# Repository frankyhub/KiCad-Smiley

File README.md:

<div align="center">

|[:skull:ISSUE](https://github.com/frankyhub/KiCad-Smiley/issues?q=is%3Aissue)|[:speech_balloon: Forum /Discussion](https://github.com/frankyhub/KiCad-Smiley/discussions)|[:grey_question:WiKi](https://github.com/frankyhub/KiCad-Smiley/wiki)||
|--|--|--|--|
| | | | |
<a href="https://github.com/frankyhub/KiCad-Smiley/issues">|<a href="https://github.com/frankyhub/KiCad-Smiley/discussions">|<a href="https://github.com/frankyhub/KiCad-Smiley/6eleases">||
|| <a href="https://github.com/frankyhub/KiCad-Smiley/pulse" alt="Activity">| <a href="https://github.com/frankyhub/KiCad-Smiley/graphs/traffic">  |<a href="https://github.com/frankyhub?tab=stars"> ||

</div>

## Smiley

<br> <br>

### BOM

| Anzahl | Bezeichnung | 
| -------- | -------- | 
|  1 |   NE555 |
| 1  |  CD4017|
| 15  |  LED rt  |
| 1  | 10uF   |
|  2 |  100R  |
| 1  | 1,2k   |
| 1  | 100k Trimmer   |
| 1  | Microschalter   |
| 2  | Batterieclipps   |
| 2  |  CR2032  |
| 1  |  Foldback-Klammern 15mm  |
| -------- | -------- | 

---

<div style="position:absolute; left:2cm; ">   
<ol class="breadcrumb" style="border-top: 2px solid black;border-bottom:2px solid black; height: 45px; width: 900px;"> <p align="center"><a href="#oben">nach oben</a></p></ol>
</div>  

---

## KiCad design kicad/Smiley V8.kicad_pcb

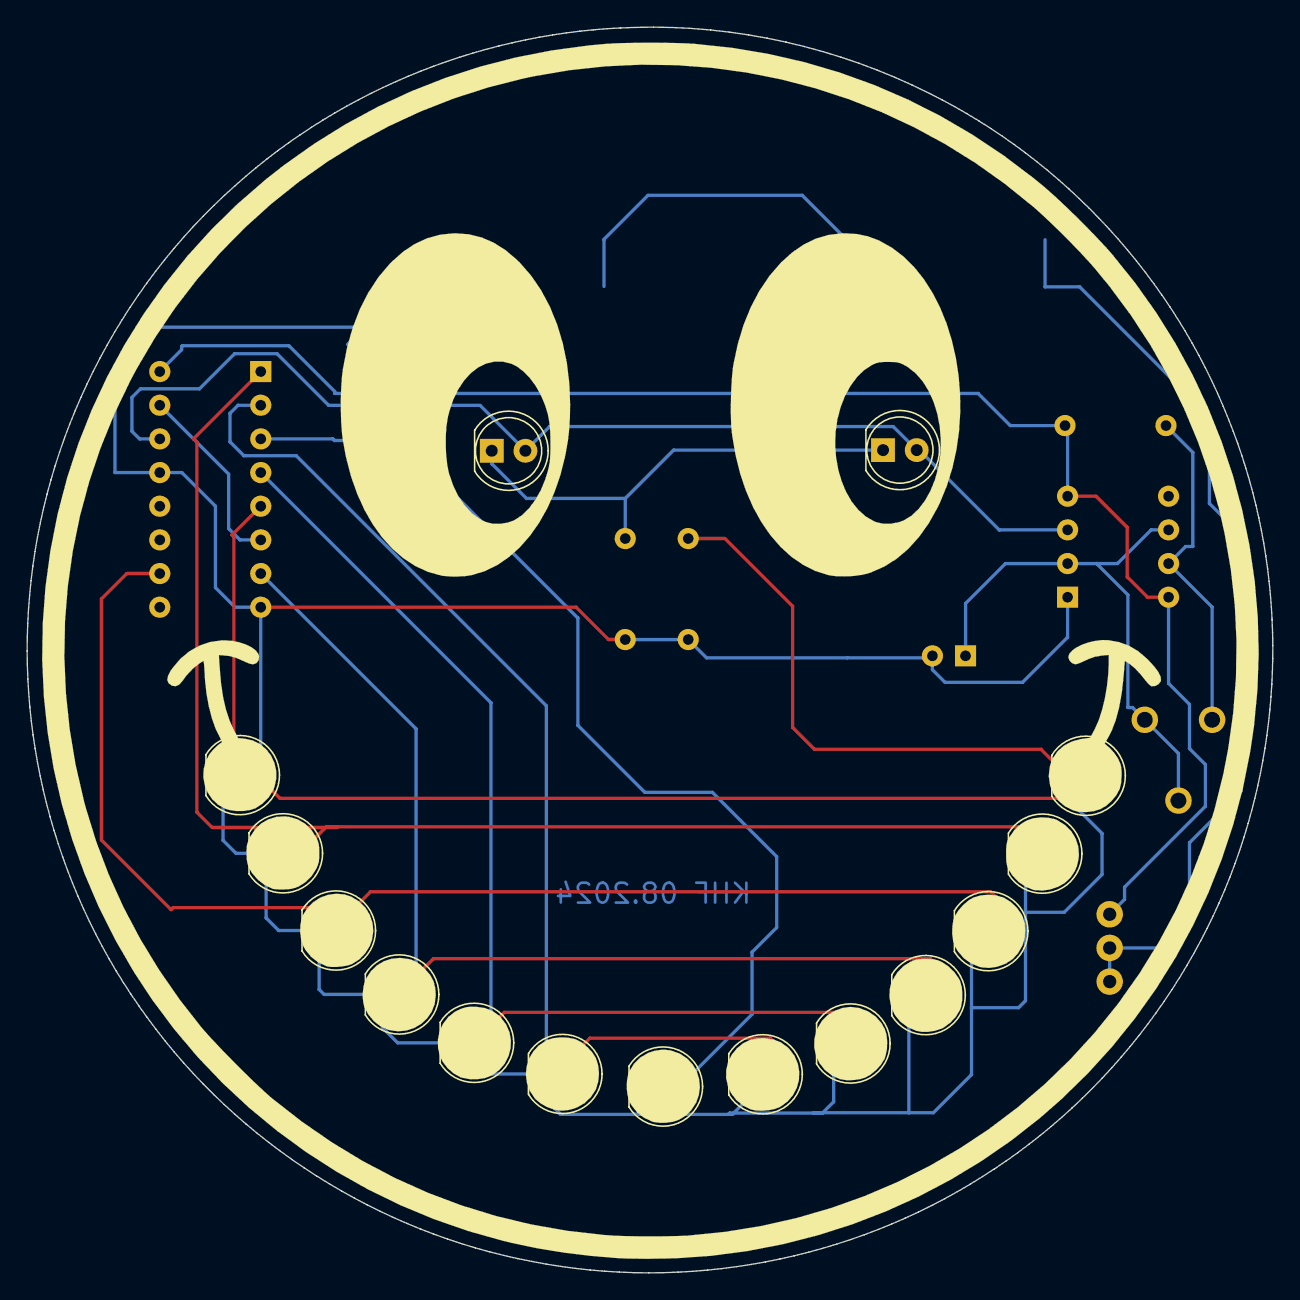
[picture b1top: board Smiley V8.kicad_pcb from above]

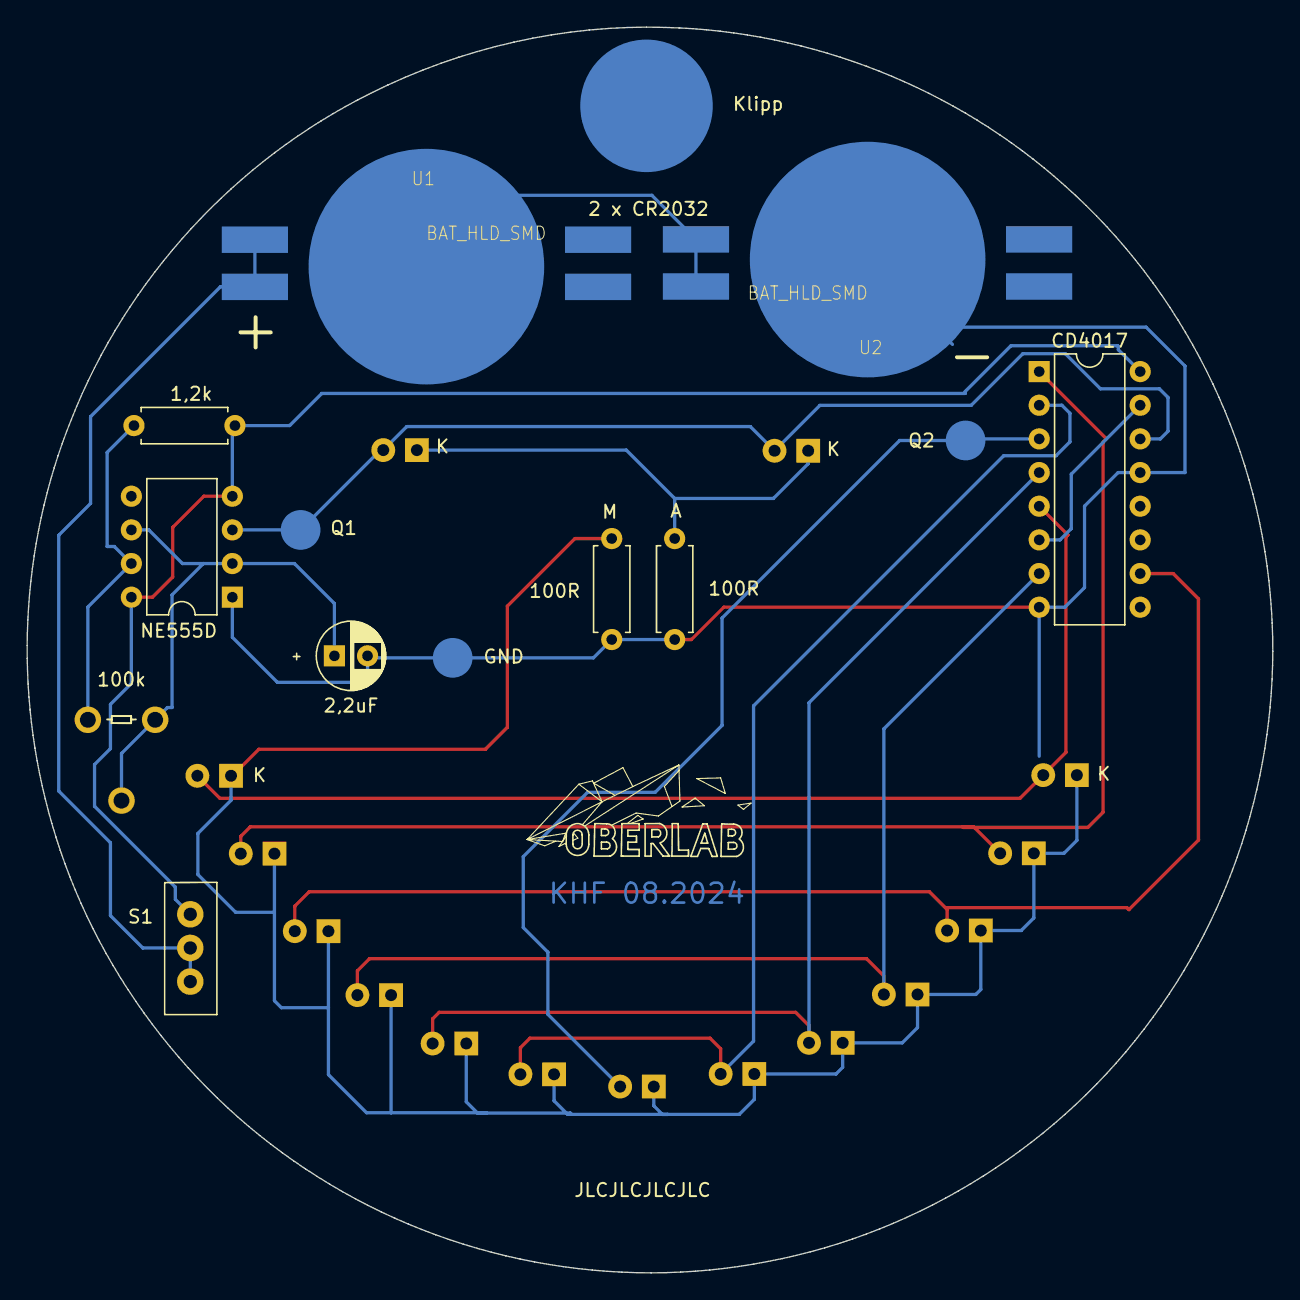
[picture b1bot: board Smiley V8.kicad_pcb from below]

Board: 2 copper layers, 94.0 x 94.0 mm, 27 parts (12 on the bottom side), 14 nets.

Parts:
C1: 2,2uF; CP_Radial_D5.0mm_P2.50mm
CD4017: 4017; DIP-16_W7.62mm
D1, D2, D3, D4, D5, D6, D7, D8, D22, D33, D44, D55, D66, D77, D88: LED; LED_D5.0mm
LP: Q1; Lötklipp
LP#2: Klipp; Lötklipp
R1: 1,2k; R_Axial_DIN0207_L6.3mm_D2.5mm_P7.62mm_Horizontal
R2: 100k; Mini-Poti
R3, R4: 100R; R_Axial_DIN0207_L6.3mm_D2.5mm_P7.62mm_Horizontal
S1: Micro_Schalter; Micro_SchalterKHF
U1, U2: BAT_HLD_SMD; BAT-HLD-SMD-Blech
U3: NE555D; DIP-8_W7.62mm

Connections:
unnamed: CD4017.3 (Q0), D1.2 (A)
unnamed: D1.1 (K), D2.1 (K), D3.1 (K), D4.1 (K), D5.1 (K), D6.1 (K), D7.1 (K), D22.1 (K), D33.1 (K), D44.1 (K), D55.1 (K), D66.1 (K), D77.1 (K), R4.1
unnamed: CD4017.2 (Q1), D2.2 (A), D22.2 (A)
unnamed: CD4017.4 (Q2), D3.2 (A), D33.2 (A)
unnamed: CD4017.7 (Q3), D4.2 (A), D44.2 (A)
unnamed: CD4017.10 (Q4), D5.2 (A), D55.2 (A)
unnamed: CD4017.1 (Q5), D6.2 (A), D66.2 (A)
unnamed: CD4017.5 (Q6), D7.2 (A), D77.2 (A)
unnamed: CD4017.14 (CLK), D8.2 (A), D88.2 (A), LP.1, U3.3 (Q)
unnamed: D8.1 (K), D88.1 (K), R3.1
unnamed: S1.2 (E), S1.3 (A), U1.1
unnamed: R1.2, R2.1, U3.7 (DIS)
unnamed: C1.2, CD4017.8 (VSS), CD4017.13 (CKEN), R3.2, R4.2, U2.2, U3.1 (GND)
unnamed: CD4017.16 (VDD), R1.1, S1.1 (A), U3.4 (R), U3.8 (VCC)

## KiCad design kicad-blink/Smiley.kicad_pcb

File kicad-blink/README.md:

## Smiley blink

### BOM

| Anzahl | Bezeichnung | 
| -------- | -------- | 
|1	|Platine|
|1	|Batteriehalter|
|1	|CR2032|
|1	|S1 Micro_Schalter|
|1	|U1 NE555|
|1|	C1 1 220uF|
|1	|D1 1N4148|
|2	|P1, P2 10k|
|2	|T1, T2 BC548|
|1	|R3 560k|
|1	|R4 390k|
|1	|R5 4k7|
|1	|R6 10R|
|15	|LED rt 5mm|
|--------	|--------|

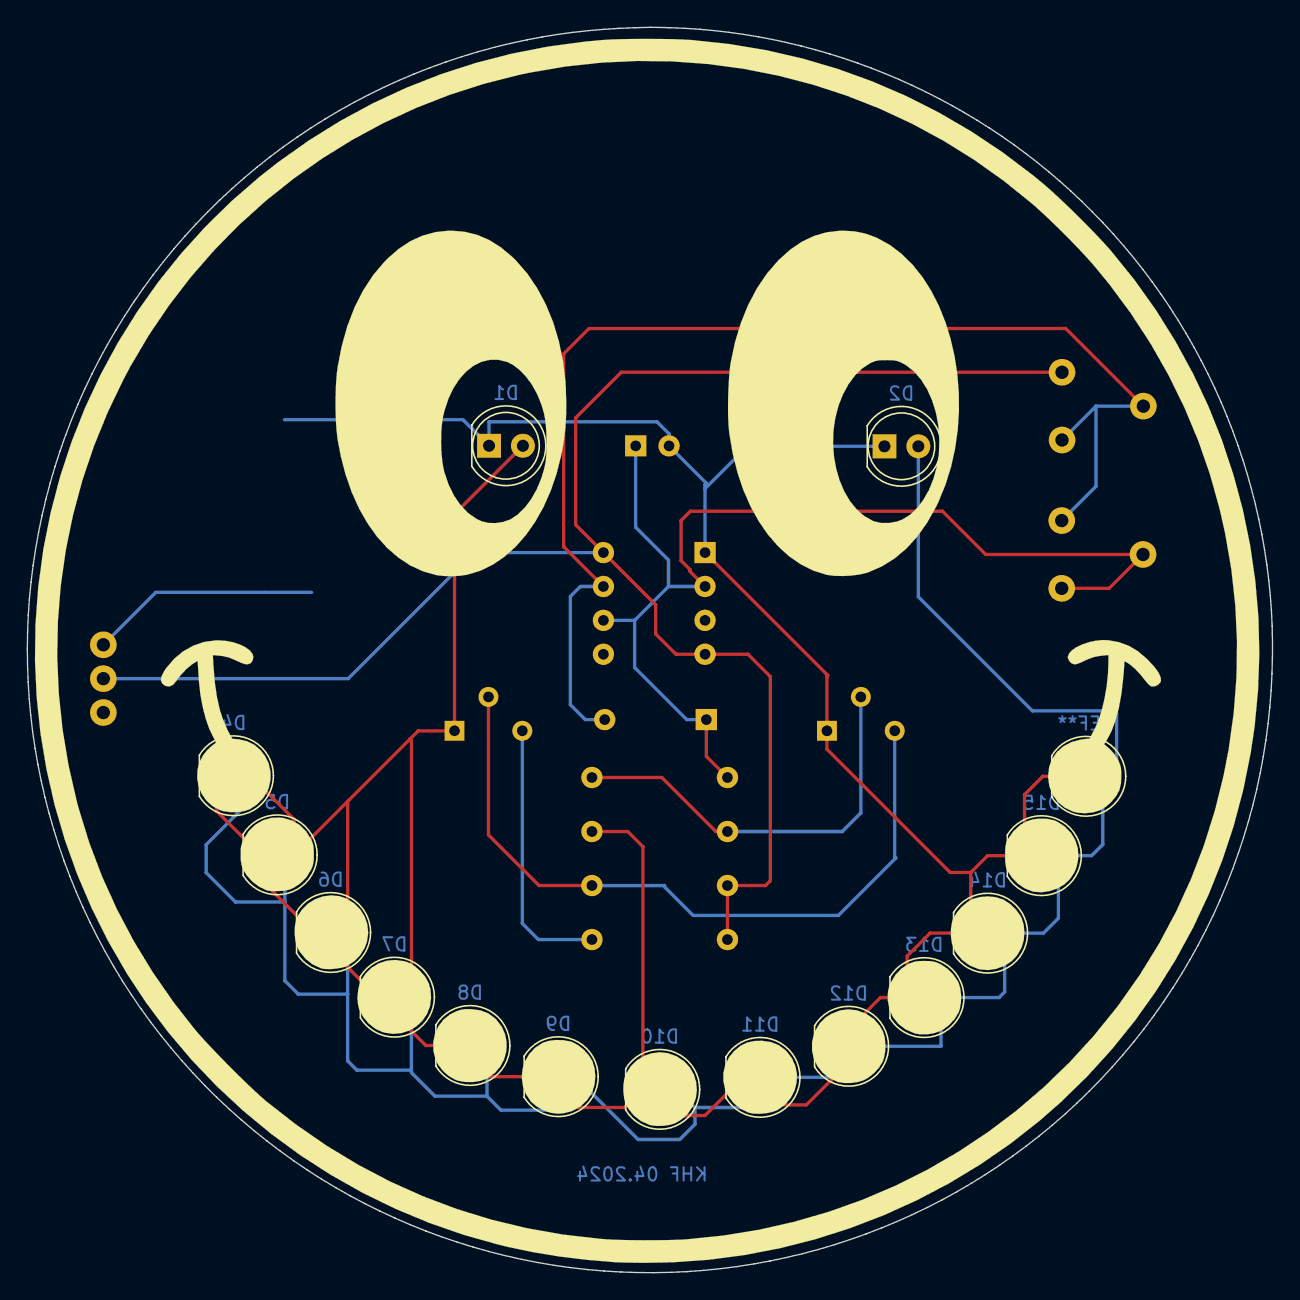
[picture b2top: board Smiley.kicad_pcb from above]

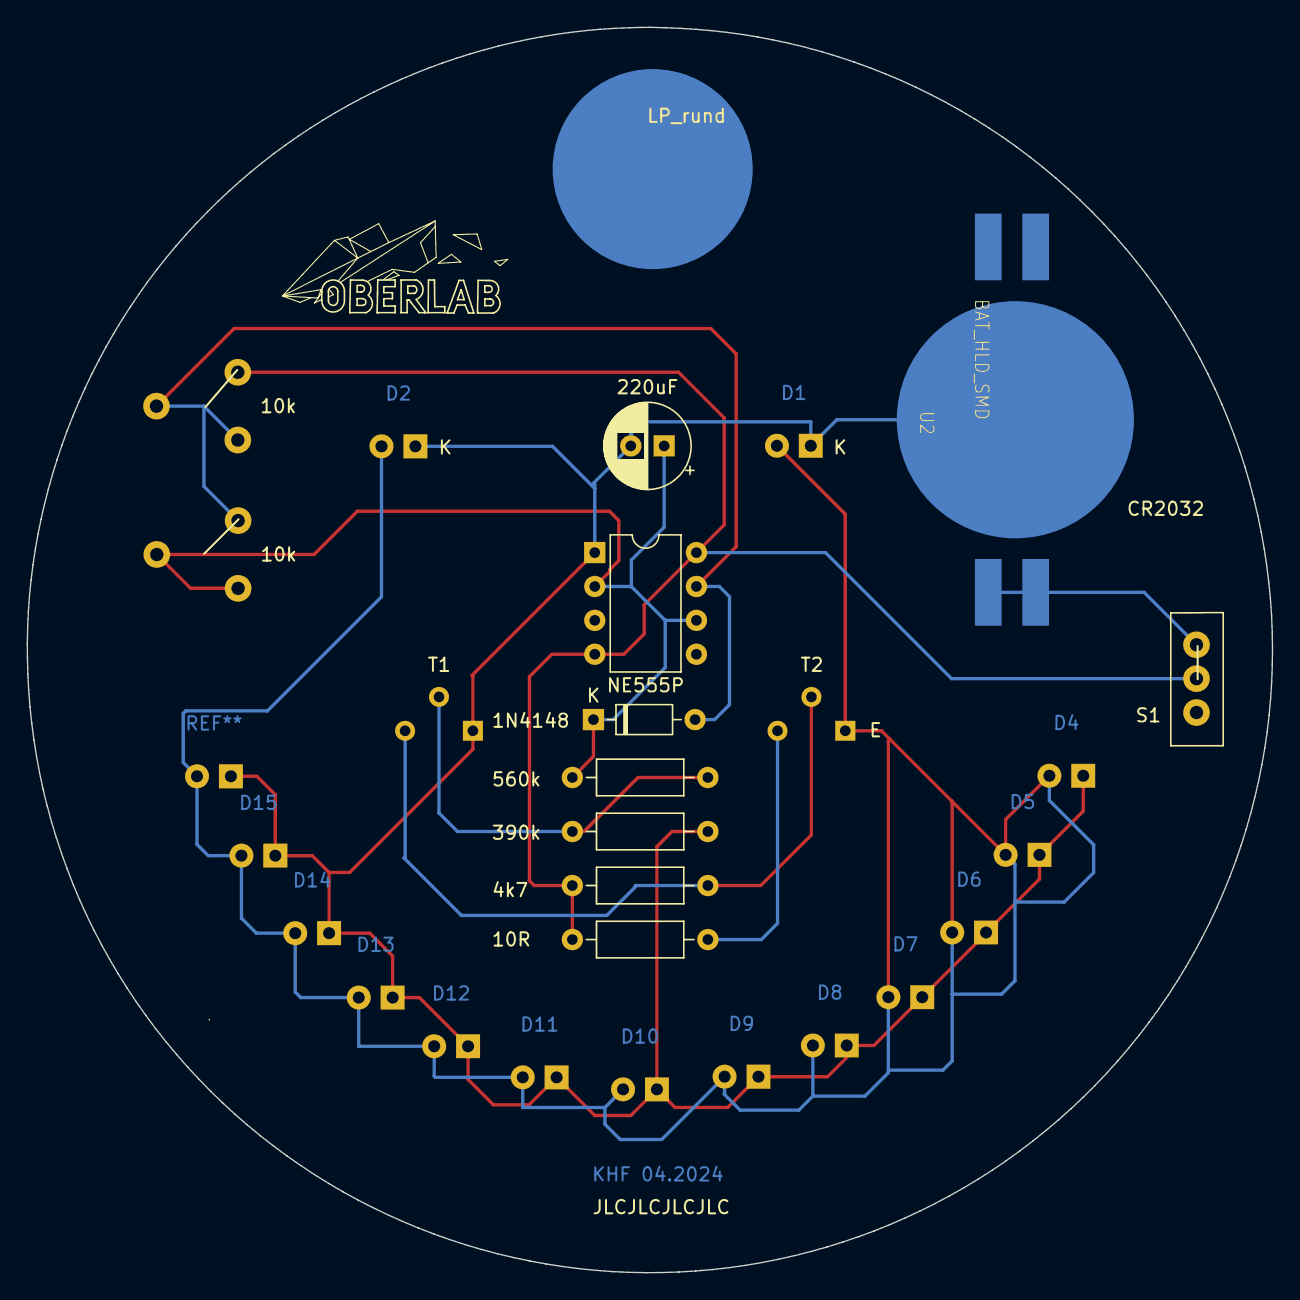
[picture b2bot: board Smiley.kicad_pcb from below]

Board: 2 copper layers, 93.3 x 93.4 mm, 28 parts (12 on the bottom side), 9 nets.

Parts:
C1: 220uF; CP_Radial_D6.3mm_P2.50mm
D1, D2, D4, D5, D6, D7, D8, D9, D10, D11, D12, D13, D14, D15: LED; LED_D5.0mm
D3: 1N4148; D_DO-35_SOD27_P7.62mm_Horizontal
LP_rund: LP_rund
P1, P2: 10k; Mini-Poti
R3: 560k; R_Axial_DIN0207_L6.3mm_D2.5mm_P10.16mm_Horizontal
R4: 390k; R_Axial_DIN0207_L6.3mm_D2.5mm_P10.16mm_Horizontal
R5: 4k7; R_Axial_DIN0207_L6.3mm_D2.5mm_P10.16mm_Horizontal
R6: 10R; R_Axial_DIN0207_L6.3mm_D2.5mm_P10.16mm_Horizontal
S1: Micro_Schalter; Micro_SchalterKHF
T1, T2: Q_NPN_EBC; TO-92L_Wide
U1: NE555P; DIP-8_W7.62mm
U2: BAT_HLD_SMD; BAT-HLD-SMD-Blech

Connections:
unnamed: D1.2 (A), D2.2 (A), D4.2 (A), D5.2 (A), D6.2 (A), D7.2 (A), D8.2 (A), D9.2 (A), D10.2 (A), D11.2 (A), D12.2 (A), D13.2 (A), D14.2 (A), D15.2 (A), T2.1 (E)
unnamed: C1.2, D1.1 (K), D2.1 (K), D4.1 (K), D5.1 (K), D6.1 (K), D7.1 (K), D8.1 (K), D9.1 (K), D10.1 (K), D11.1 (K), D12.1 (K), D13.1 (K), D14.1 (K), D15.1 (K), R4.2, T1.1 (E), U1.1 (GND), U2.2
unnamed: D3.2 (A), P1.2, P1.3, P2.1, U1.7 (DIS)
unnamed: C1.1, D3.1 (K), P2.2, P2.3, R3.1, U1.2 (TR), U1.6 (THR)
unnamed: S1.1 (A), U2.1
unnamed: P1.1, R5.1, R6.1, S1.2 (E), U1.4 (R), U1.8 (VCC)
unnamed: R3.2, R4.1, T1.2 (B)
unnamed: R5.2, T1.3 (C), T2.2 (B)
unnamed: R6.2, T2.3 (C)

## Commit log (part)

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2024-02-28 V 01.2024
2024-02-28 V 1.2024
2024-02-28 V1.1 01.2024
2024-02-28 10uF Update README.md
2024-02-28 Foldback-Klammern 15mm Update README.md
2024-02-28 ´V1.2 01.2024
2024-04-02 4017 Update README.md
2024-04-02 V1.2 02.04.2024
2024-04-04 V2.0 04.04.2024
2024-04-04 V2 04.04.2024
2024-04-06 V 06.04.2024
2024-04-06 Rename README to README.md
2024-04-14 V2 14.04.2024
2024-05-09 V 08.05.2024
2024-05-18 V 18.ß5.2024
2024-06-01 V 01.06.24
2024-08-08 V 08082024 2
2024-10-12 V12102024
